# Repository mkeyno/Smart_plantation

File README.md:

# Smart Plantation

My country has limited water resources while most of the farmssteel using the old methods for farming and irrigation. Most of the plantation using 3phase electrical motor for pulling water from deep well, This motor put a heavy load on the electrical grid and the government triedto encourage the farmers to not use the electricity in high peak hours on thegrid by subsidizing those farms which use the electricity in  not rush hours This Repository consists of the hardware and firmware for controllingthe farm water & electricity usage base on IoT technology. The different scenarios can be  set by owners of the plantation regards to the information that comes from the water pumpirrigation systems and lands. 
Water irrigation system consist electrical pump for the well & storagepool, all electrical actuator valve, sensors for soil humidity  and water level in wellSoil humidity detects by a low-power solar humidity sensor equipped with an nRF24lP low power transmitter.Every 3 hours sample of humidity sends to the main unit. Different scenarios base onwater level, time, total electricity consumption will be trigged and report to the landowner via SMS

# Hardware

This controller consists of 4 main modules, 
  - ESP8266 for IoTinterface and local webserver for setting up the plantation control and select a  variety of scenario  
  
  - SIM700 GSM/GPRSmodule for remote control of plantation with a variety of predefined SMS commandwhich is authenticated by mobile number 
  
  - nRF24Lp lowpower transmitter link for gathering data of humidity sensors across theplantation
  
  - STM32F103C8module for handling all sub-control routines such as all valve actuators andmotors and get all sensor information from soil humidity sensor and ultrasonicwater level sensor. 
  
This module activates the electrical motors regards thesensor data and scenario which has been defined by the landowner. To monitor power consumption and power factor of electricalmotors, three ST sensors for measuring the current of each phase, and one transformer formeasuring the voltage of lines has been considered
following are the image of the designed PCB 

,,

# Firmware

Two MCUs were used in this design, one ESP8266 as pilot controland data link  for local webserver and one STM32F103C8 forcontrolling the plantation, these MCUs communicate together via I2C protocol inmaster-slave modeESP8266 can restart the STM32F103C8 and adjust the setting byIOT webserver portal, the following image showing the different pages which designedfor different parts of the controller

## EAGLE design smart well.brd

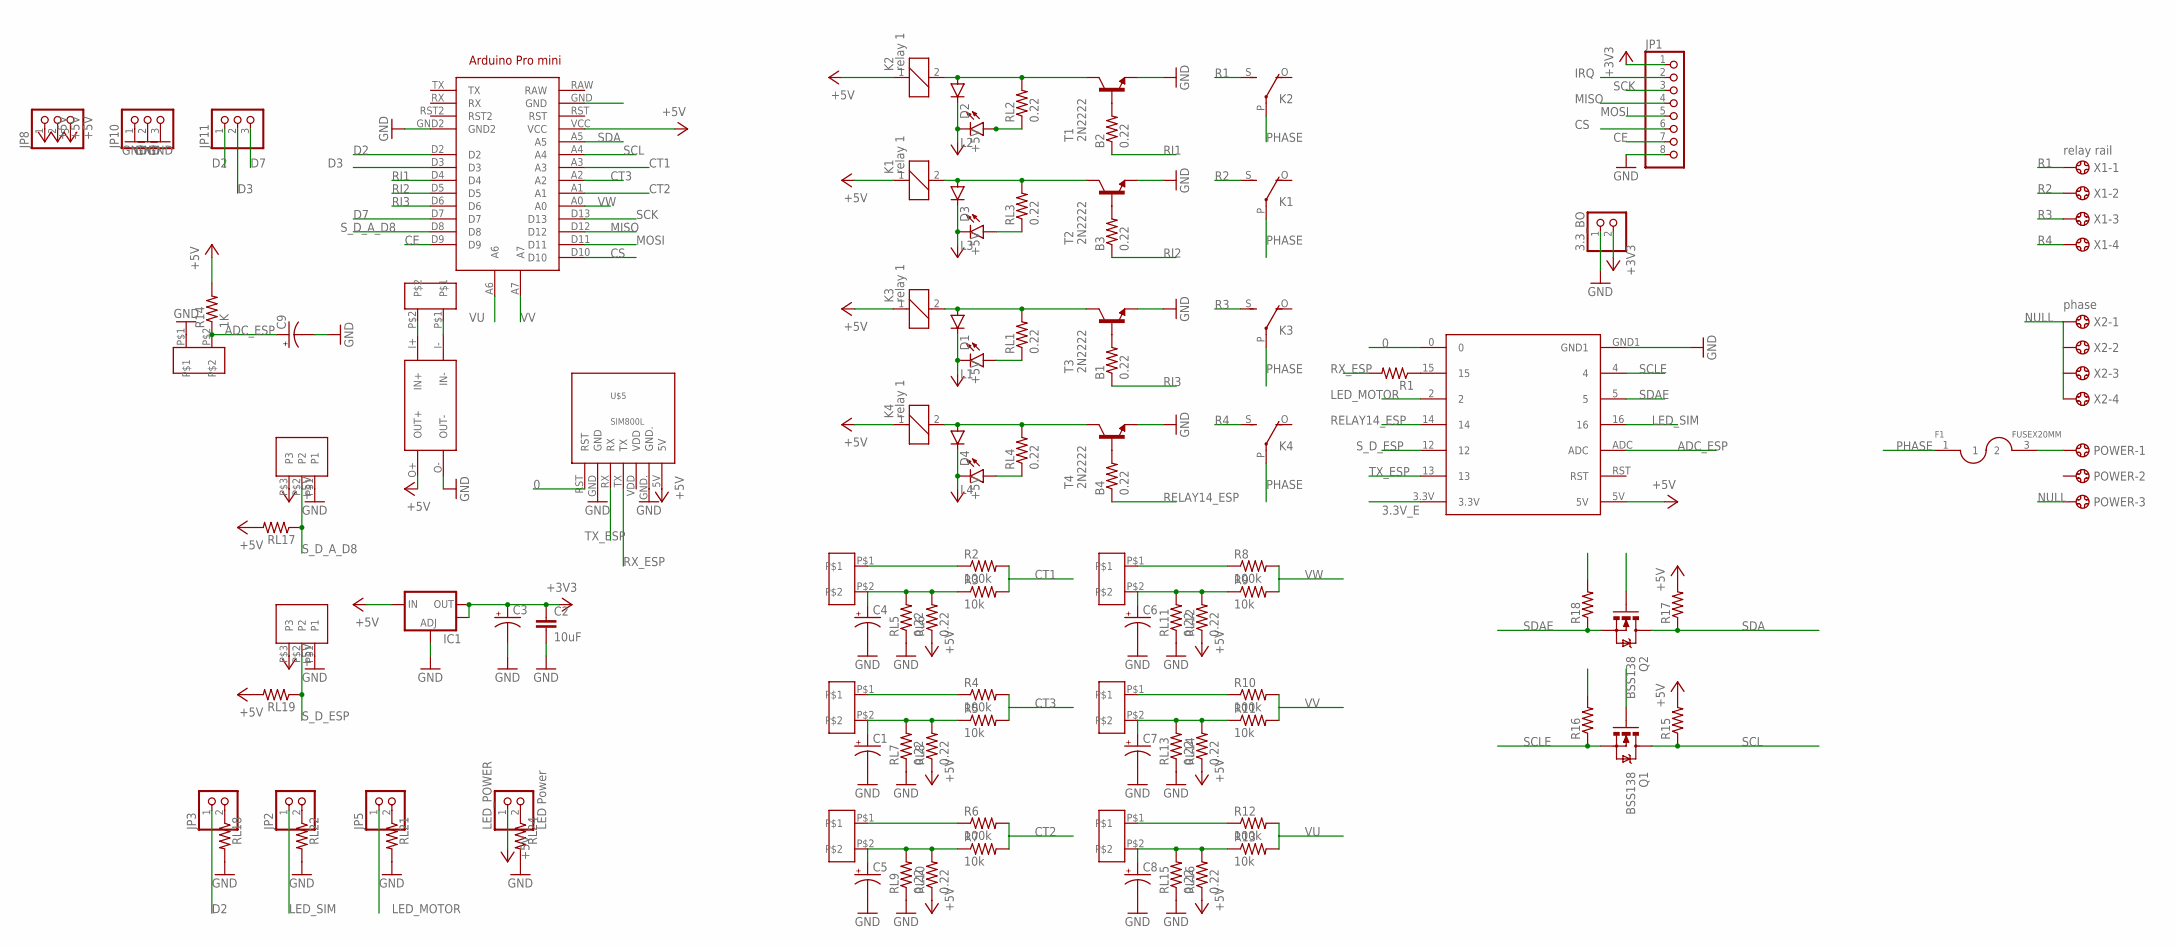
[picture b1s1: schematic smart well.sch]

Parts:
3.3_BO: PINHD-1X2; 1X02
B1, B2, B3, B4: 0.22; 0805
C1, C3, C4, C5, C6, C7, C8: 100UF-25V-20%(PTH); CPOL-RADIAL-100UF-25V
C2: 10uF; 1210
C9: 10UF-25V-20%(PTH)KIT; CPOL-RADIAL-10UF-25V-KIT
CT1, CT2, CT3, CT4, CT5, CT6: ct1; PIN_LOCK1X2
D1, D2, D3, D4: DIODEKIT2; DIODE-1N4001-KIT
F1: FUSEX20MM; FUSE_5MM
IC1: V_REG_LM1117SOT223; SOT223
JP1: PINHD-1X8; 1X08
JP2, JP3, JP5: PINHD-1X2; 1X02
JP8, JP10, JP11: PINHD-1X3; 1X03
K1, K2, K3, K4: relay 1; G5LE
L1, L2, L3, L4: LED3MM
LED_POWER: LED Power; 1X02
POWER: 5202-03-N-02
Q1, Q2: BSS138; SOT23-3
R1: 0.3OHM-1/8W-1%(0805); 0805
R2, R4, R6, R8, R10, R12: 100k; AXIAL-0.1
R3, R5, R7, R9, R11, R13: 10k; AXIAL-0.1
R14: 1K; AXIAL-0.1
R15, R16, R17, R18: 0.22OHM-1/4W-1%(0805); 0805
RL1, RL2, RL3, RL4, RL5, RL6, RL7, RL8, RL9, RL10, RL11, RL12, RL13, RL14, RL15, RL16: 0.22; 0805
RL17, RL18, RL19, RL21, RL22, RL24: 0.22OHM-1/4W-1%(0805); 0805
T1, T2, T3, T4: 2N2222; TO92-EBC-OVAL
U$2, U$8: PIN_LOCK_1X3; PIN_LOCK1X3
U$3: ESP12F_SHEILD10PIN
U$5: SIM800L
U$6: DC-DC
U$7: ARDUINO_DIP
U$9, U$11: PIN_LOCK_1X2; PIN_LOCK1X2
X1: relay rail; 5202-04-N-02
X2: phase; 5202-04-N-02

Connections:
0: U$3.0, U$5.RST
3.3V_E: Q1.1 (G), Q2.1 (G), R16.2, R18.2, U$3.3.3V
+3V3: 3.3_BO.2, C2.1, C3.1 (+), IC1.2 (OUT), IC1.4 (OUT), JP1.1
+5V: D1.C, D2.C, D3.C, D4.C, IC1.3 (IN), JP8.1, JP8.2, JP8.3, K1.1, K2.1, K3.1, K4.1, L1.K (C), L2.K (C), L3.K (C), L4.K (C), LED_POWER.1, R14.P$2 (2), R15.2, R17.2, RL6.1, RL8.1, RL10.1, RL12.1, RL14.1, RL16.1, RL17.2, RL19.2, U$2.P$3 (P3), U$3.5V, U$5.5V, U$6.O+ (OUT+), U$7.VCC, U$8.P$3 (P3)
ADC_ESP: C9.1 (+), R14.P$1 (1), U$3.ADC, U$11.P$2
CE: JP1.7, U$7.D9
CS: JP1.6, U$7.D10
CT1: R2.P$2 (2), R3.P$2 (2), U$7.A3
CT2: R6.P$2 (2), R7.P$2 (2), U$7.A1
CT3: R4.P$2 (2), R5.P$2 (2), U$7.A2
D2: JP3.1, JP11.1, U$7.D2
D3: JP11.2, U$7.D3
D7: JP11.3, U$7.D7
GND: 3.3_BO.1, C1.2 (-), C2.2, C3.2 (-), C4.2 (-), C5.2 (-), C6.2 (-), C7.2 (-), C8.2 (-), C9.2 (-), IC1.1 (ADJ), JP1.8, JP10.1, JP10.2, JP10.3, RL5.1, RL7.1, RL9.1, RL11.1, RL13.1, RL15.1, RL18.2, RL21.2, RL22.2, RL24.2, T1.E, T2.E, T3.E, T4.E, U$2.P$1 (P1), U$3.GND1, U$5.GND, U$5.GND., U$6.O- (OUT-), U$7.GND2, U$8.P$1 (P1), U$11.P$1
IRQ: JP1.2
LED_MOTOR: JP5.1, U$3.2
LED_SIM: JP2.1, U$3.16
MISO: JP1.4, U$7.D12
MOSI: JP1.5, U$7.D11
unnamed: R1.1, U$3.15
unnamed: U$6.I+ (IN+), U$9.P$2
unnamed: D2.A, K2.2, RL2.2, T1.C
unnamed: D3.A, K1.2, RL3.2, T2.C
unnamed: B2.2, T1.B
unnamed: B3.2, T2.B
unnamed: L2.A, RL2.1
unnamed: L3.A, RL3.1
unnamed: F1.3 (2), POWER.1
unnamed: D1.A, K3.2, RL1.2, T3.C
unnamed: L1.A, RL1.1
unnamed: B1.2, T3.B
unnamed: D4.A, K4.2, RL4.2, T4.C
unnamed: L4.A, RL4.1
unnamed: B4.2, T4.B
unnamed: U$6.I- (IN-), U$9.P$1
unnamed: CT2.P$1, R4.P$1 (1)
unnamed: CT1.P$1, R2.P$1 (1)
unnamed: C4.1 (+), CT1.P$2, R3.P$1 (1), RL5.2, RL6.2
unnamed: C1.1 (+), CT2.P$2, R5.P$1 (1), RL7.2, RL8.2
unnamed: CT3.P$1, R6.P$1 (1)
unnamed: C5.1 (+), CT3.P$2, R7.P$1 (1), RL9.2, RL10.2
unnamed: CT4.P$1, R8.P$1 (1)
unnamed: C6.1 (+), CT4.P$2, R9.P$1 (1), RL11.2, RL12.2
unnamed: CT5.P$1, R10.P$1 (1)
unnamed: C7.1 (+), CT5.P$2, R11.P$1 (1), RL13.2, RL14.2
unnamed: CT6.P$1, R12.P$1 (1)
unnamed: C8.1 (+), CT6.P$2, R13.P$1 (1), RL15.2, RL16.2
unnamed: JP5.2, RL21.1
unnamed: JP2.2, RL22.1
unnamed: LED_POWER.2, RL24.1
unnamed: JP3.2, RL18.1
NULL: POWER.3, X2.1, X2.2, X2.3, X2.4
PHASE: F1.1, K1.P, K2.P, K3.P, K4.P
R1: K2.S, X1.1
R2: K1.S, X1.2
R3: K3.S, X1.3
R4: K4.S, X1.4
RELAY14_ESP: B4.1, U$3.14
RI1: B2.1, U$7.D4
RI2: B3.1, U$7.D5
RI3: B1.1, U$7.D6
RX_ESP: R1.2, U$5.TX
SCK: JP1.3, U$7.D13
SCL: Q1.3 (D), R15.1, U$7.A4
SCLE: Q1.2 (S), R16.1, U$3.4
SDA: Q2.3 (D), R17.1, U$7.A5
SDAE: Q2.2 (S), R18.1, U$3.5
S_D_A_D8: RL17.1, U$2.P$2 (P2), U$7.D8
S_D_ESP: RL19.1, U$3.12, U$8.P$2 (P2)
TX_ESP: U$3.13, U$5.RX
VU: R12.P$2 (2), R13.P$2 (2), U$7.A6
VV: R10.P$2 (2), R11.P$2 (2), U$7.A7
VW: R8.P$2 (2), R9.P$2 (2), U$7.A0

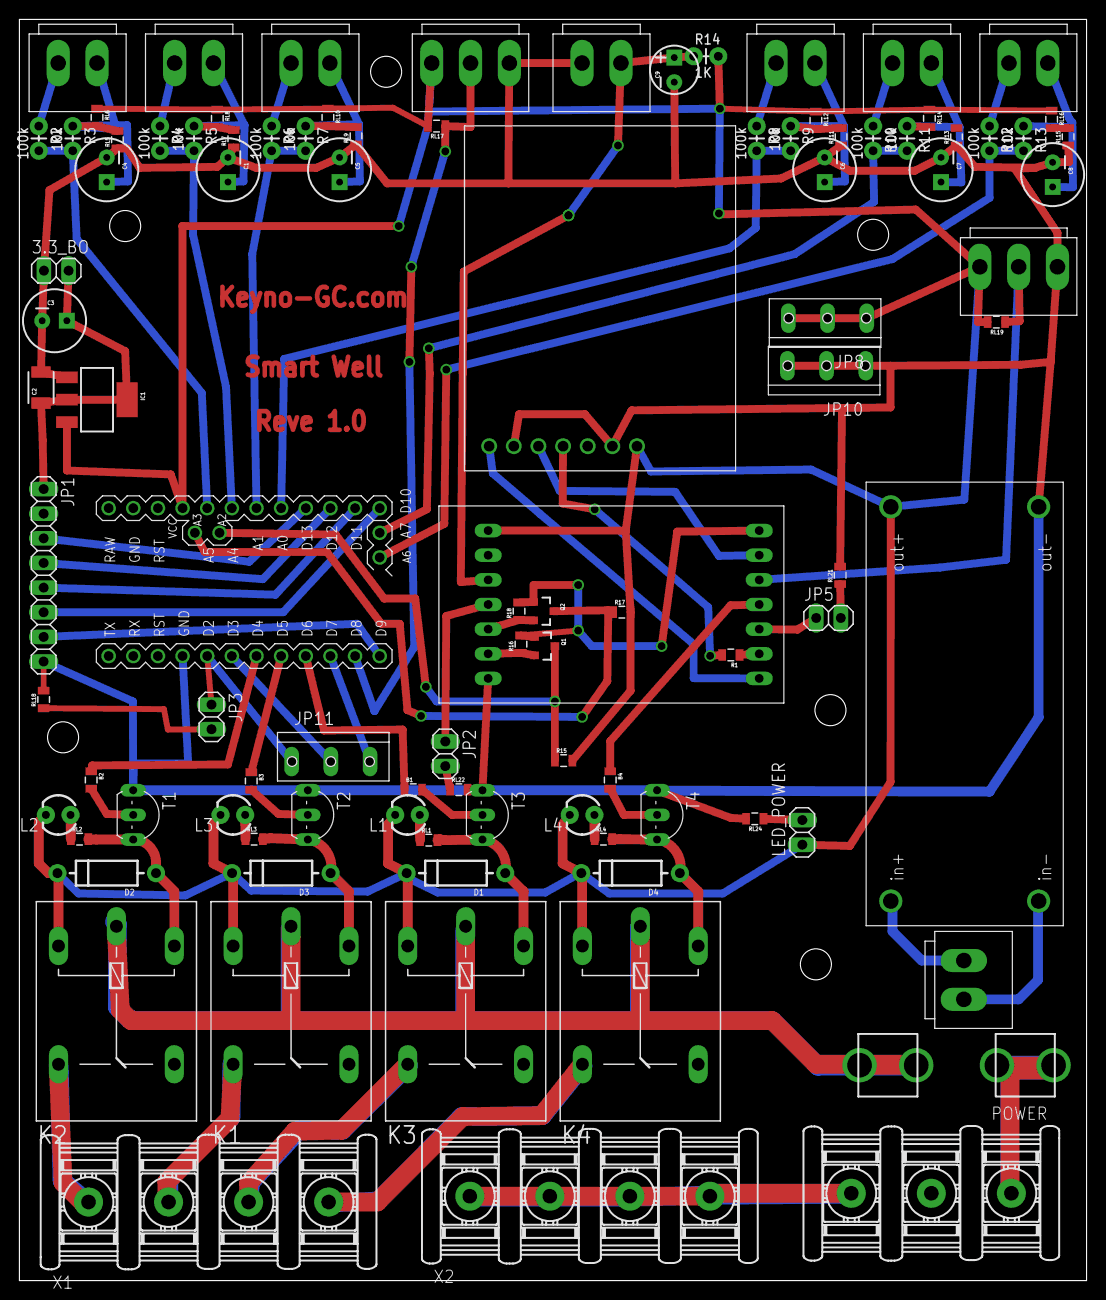
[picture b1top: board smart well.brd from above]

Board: 2 copper layers, 110.0 x 130.0 mm, 99 parts (0 on the bottom side), 72 nets.

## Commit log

2019-02-04 updated with new board
2021-09-03 Rename smart well.brd to hardware/smart well.brd
2021-09-03 Rename smart well.sch to hardware/smart well.sch

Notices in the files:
parts and their libraries:
SparkFun-PowerIC: Licensing: Creative Commons ShareAlike 4.0 International - https://creativecommons.org/licenses/by-sa/4.0
